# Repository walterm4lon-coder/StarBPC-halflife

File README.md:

# Starbie!
This is my first ever hardware project!

## What is it?
This is starbie, my digital pet, that can react to the enviroment using a scensor. He can be scared, chill, sleep, or be played with or fed!
its based on XIAO ESP32-C3 and has a tiny OLED display,environmental sensor, and interactive buttons.

## Features
animated pixel cat: https://last-tick.itch.io/animated-pixel-kittens-cats-32x32
interactive Menu: NAP, PLAY, FEED, and PET.
motion detector
environmental sensors
custom PCB

## Hardware:
XIAO ESP32-C3, SSD1306 128×64 OLED, MPU6050, DHT11, 2 push buttons, custom PCB

## Made for hackclub Halflife
Respect guys! love u

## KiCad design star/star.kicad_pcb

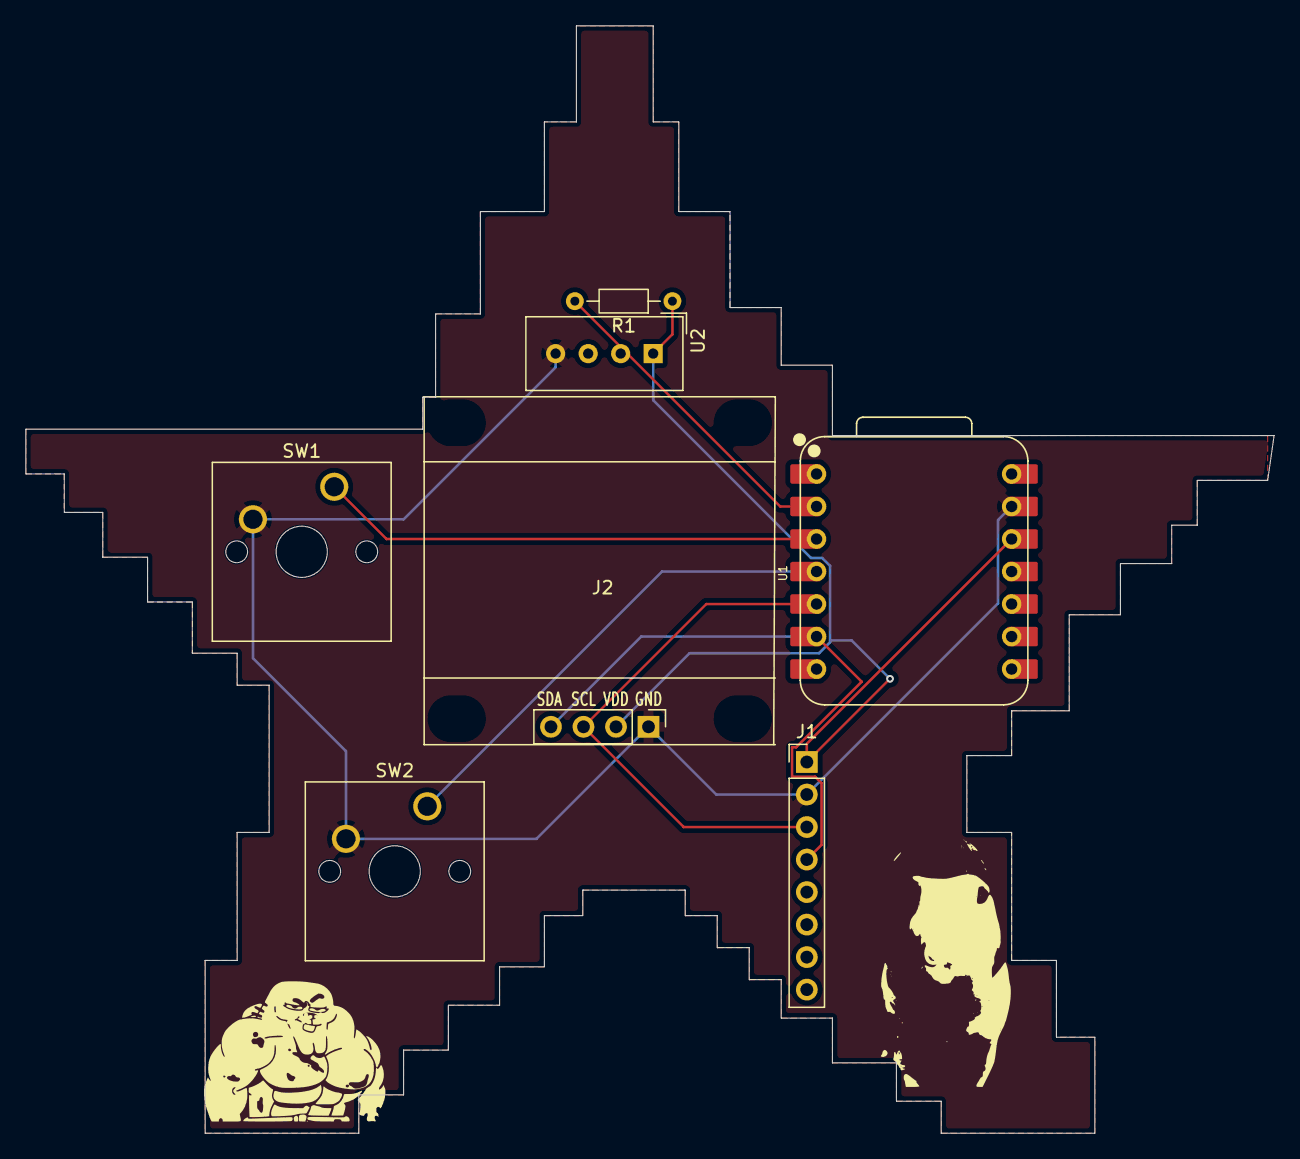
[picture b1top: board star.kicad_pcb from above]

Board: 2 copper layers, 97.5 x 86.5 mm, 7 parts (0 on the bottom side), 7 nets.

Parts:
J1: Conn_01x08_Pin; PinHeader_1x08_P2.54mm_Vertical
J2: Conn_01x04_Pin; Display_128x64_096_I2C
R1: 10k; R_Axial_DIN0204_L3.6mm_D1.6mm_P7.62mm_Horizontal
SW1, SW2: SW_Push; SW_Cherry_MX_1.00u_PCB
U1: XIAO-ESP32-C3-SMD; XIAO-ESP32-C6-DIP
U2: DHT11; Aosong_DHT11_5.5x12.0_P2.54mm

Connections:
+3.3V: J1.1, J2.2, R1.1, U1.12 (3V3_OUT), U2.1 (VDD)
/DHT11 DATA: R1.2, U1.2 (D1), U2.2 (DATA)
/GPI02: SW1.1, U1.3 (D2)
/GPI03: SW2.1, U1.4 (D3)
/SCL: J1.3, J2.3, U1.5 (D4)
/SDA: J1.4, J2.4, U1.6 (D5)
GND: J1.2, J2.1, SW1.2, SW2.2, U1.13 (GND), U2.4 (GND)
